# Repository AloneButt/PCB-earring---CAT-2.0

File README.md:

# 🐱 Kitty Blinky Earrings

This project is a **pair of kitty-shaped PCBs** designed as earrings for my beloved wife 💖.  
Each earring is powered by a CR2032 coin cell and blinks two LEDs in an alternating pattern (classic astable multivibrator style 🟡🟢).  

It’s a mix of **electronics + wearable art**, made as a gift 💝.

## 🥂 Shoutout to the sponsor of the project

<p align="center">
  
</p>

<p align="center">
  This project was proudly prototyped with support from
  <a href="https://www.pcbway.com/?from=github"><b>PCBWay</b></a>.<br>
  Their precision manufacturing, excellent finish quality, and quick lead times made this build possible.
  Check out their site and PCB manufacturing capabilities and good luck!
</p>

---

## ✨ Features
- Kitty-shaped PCB outline 😺
- Two LEDs blinking one after another (0.5 Hz)
- Powered by a CR2032 battery (≈220 mAh)
- Minimal BOM (two transistors, resistors, capacitors, LEDs, battery holder)
- Works as earrings or just a tiny blinking desk buddy

---

## 🛠️ How It Works
- Simple transistor astable multivibrator  
- No microcontroller, no 555 timer, just pure retro discrete-component charm  
- Each side alternately lights an LED, making the kitty “sparkle”

---

## 🎁 Why?
Because sometimes the best gifts are the ones you solder yourself ❤️

---

## 🧩 Folder Contents (not ready yet)
- `schematic/` → KiCAD schematic files  
- `pcb/` → KiCAD PCB layout (kitty outline!)  
- `gerbers/` → Production files to send to a fab  
- `3d/` → Renders of the finished board  
- `docs/` → Pictures and notes  

---

## ⚡ BOM (Bill of Materials)
| Part | Qty | Notes |
|------|-----|-------|
| 2N3904U transistor | 2 | NPN |
| Resistors | 5 | LED current limiting + timing |
| Capacitors | 2 | 10 µF timing caps |
| LEDs | 2 | SMD 0805 (color of choice) |
| CR2032 battery holder | 1 | Top-mount or back-mount |
| PCB | 1 | Kitty shaped 🐾 |

---

## 📸 Preview

## 3D

## PCB

## Video

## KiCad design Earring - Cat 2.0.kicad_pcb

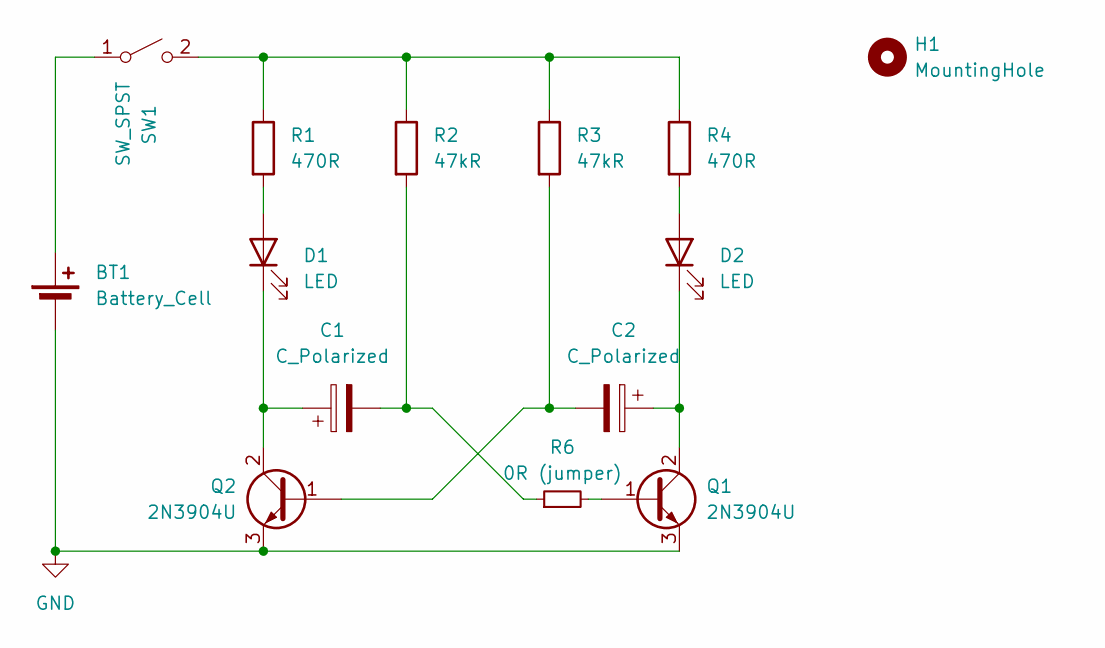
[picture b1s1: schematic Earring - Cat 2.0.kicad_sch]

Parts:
BT1: Battery_Cell; BATTERY holder CR2032 SMD
C1, C2: C_Polarized; C_0805_2012Metric
D1, D2: LED; LED_1206_3216Metric
H1: MountingHole; MountingHole_2.2mm_M2_DIN965_Pad
Q1, Q2: 2N3904U; SOT-89-3
R1, R4: 470R; R_0805_2012Metric
R2, R3: 47kR; R_0805_2012Metric
R6: 0R (jumper); R_0805_2012Metric
SW1: SW_SPST; DIP switch 1P THT

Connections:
GND: BT1.2 (-), Q1.3 (E), Q2.3 (E)
unnamed: BT1.1 (+), SW1.1 (A)
unnamed: C1.2, R2.2, R6.1
unnamed: D1.2 (A), R1.2
unnamed: C1.1, D1.1 (K), Q2.2 (C)
unnamed: D2.2 (A), R4.2
unnamed: C2.1, D2.1 (K), Q1.2 (C)
unnamed: Q1.1 (B), R6.2
unnamed: C2.2, Q2.1 (B), R3.2
unnamed: R1.1, R2.1, R3.1, R4.1, SW1.2 (B)

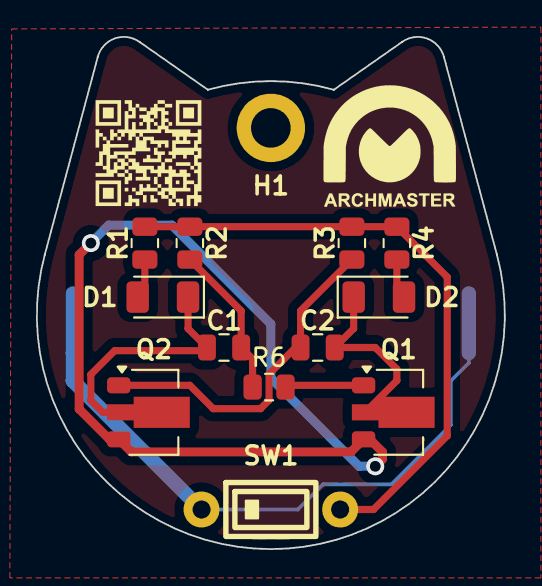
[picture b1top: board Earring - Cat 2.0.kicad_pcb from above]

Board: 2 copper layers, 26.0 x 28.5 mm, 14 parts (1 on the bottom side), 10 nets.

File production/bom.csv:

Designator,Footprint,Quantity,Value,LCSC Part #
BT1,BATTERY holder CR2032 SMD,1,Battery_Cell,
"C1, C2",0805,2,C_Polarized,
"D1, D2",1206,2,LED,
"Q1, Q2",SOT-89-3,2,2N3904U,
"R1, R4",0805,2,470R,
"R2, R3",0805,2,47kR,
R6,0805,1,0R (jumper),
SW1,DIP switch 1P THT,1,SW_SPST,

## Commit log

2025-10-02 readme
2025-10-03 render
2025-10-03 edit readme
2025-10-08 updated the silkscreen
2025-10-08 updated production
2025-10-25 boards fabricated
2025-11-20 updated prod and media
